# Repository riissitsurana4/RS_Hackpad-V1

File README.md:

# RS_Hackpad-V1

Hello everyone!
This is my first hardware project, built as part of **Blueprint (Hack Club)**.

It is a custom macropad made using switches, a rotatory encoder, oled display, etc.

---

## Case Design

The case consists of **two 3D-printed parts**

* **Top plate**
* **Base case**

---

## PCB Design

The PCB was designed in **KiCad** and includes the following features:

* **8 mechanical switches** arranged in a matrix (4 columns × 2 rows)
* **8 SK6812 RGB LEDs** for underglow
* **1 rotary encoder**
* **0.91 inch OLED display**
* **Seeed XIAO RP2040** as the MCU

The LEDs are placed near the edges of the PCB to create an underglow effect through the case.

---
## Final Design
Arranged 3D version of all the parts including the pcb.

---

## Firmware

I have made the firmware using **KMK**. 

I have only made basic firmware as it is very confusing and i do not have anything to test on.

---

## BOM

Seeed XIAO RP2040 

Through-hole 1N4148 Diodes (x9)

MX-Style switches (x8)

EC11 Rotary encoders (x1)

0.91 inch OLED displays

SK6812 MINI-E LEDs (x8)

M3x16mm screws & M3x5mx4mm heatset inserts

---

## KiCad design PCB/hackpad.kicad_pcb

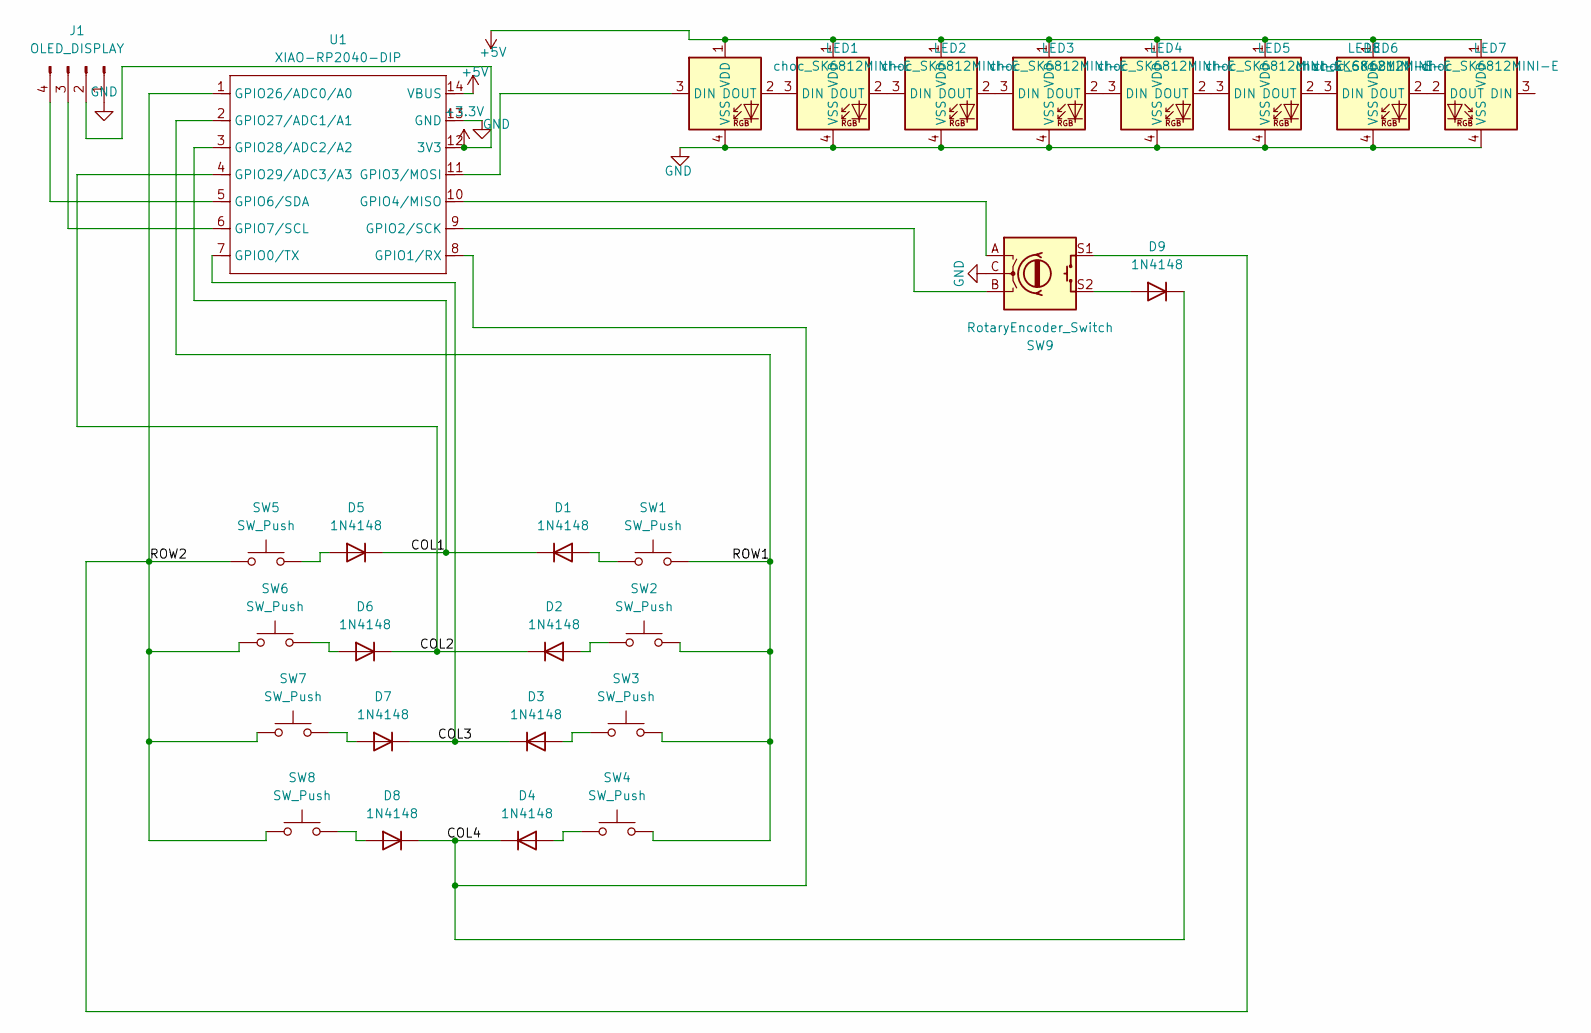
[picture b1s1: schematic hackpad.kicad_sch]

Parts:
D1, D2, D3, D4, D5, D6, D7, D8, D9: 1N4148; D_DO-35_SOD27_P7.62mm_Horizontal
J1: OLED_DISPLAY; PinHeader_1x04_P2.54mm_Vertical
LED1, LED2, LED3, LED4, LED5, LED6, LED7, LED8: choc_SK6812MINI-E; LED_SK6812MINI_PLCC4_3.5x3.5mm_P1.75mm
SW1, SW2, SW3, SW4, SW5, SW6, SW7, SW8: SW_Push; SW_Cherry_MX_1.00u_PCB
SW9: RotaryEncoder_Switch; RotaryEncoder_Alps_EC11E-Switch_Vertical_H20mm
U1: XIAO-RP2040-DIP

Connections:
+3.3V: J1.2, U1.12 (3V3)
+5V: LED1.1 (VDD), LED2.1 (VDD), LED3.1 (VDD), LED4.1 (VDD), LED5.1 (VDD), LED6.1 (VDD), LED7.1 (VDD), LED8.1 (VDD), U1.14 (VBUS)
/COL1: D1.1 (K), D5.1 (K), U1.3 (GPIO28/ADC2/A2)
/COL2: D2.1 (K), D6.1 (K), U1.4 (GPIO29/ADC3/A3)
/COL3: D3.1 (K), D7.1 (K), U1.7 (GPIO0/TX)
/COL4: D4.1 (K), D8.1 (K), D9.1 (K), U1.8 (GPIO1/RX)
/ROW1: SW1.1, SW2.1, SW3.1, SW4.1, U1.2 (GPIO27/ADC1/A1)
/ROW2: SW5.1, SW6.1, SW7.1, SW8.1, SW9.S1, U1.1 (GPIO26/ADC0/A0)
GND: J1.1, LED1.4 (VSS), LED2.4 (VSS), LED3.4 (VSS), LED4.4 (VSS), LED5.4 (VSS), LED6.4 (VSS), LED7.4 (VSS), LED8.4 (VSS), SW9.C, U1.13 (GND)
unnamed: D1.2 (A), SW1.2
unnamed: D2.2 (A), SW2.2
unnamed: D3.2 (A), SW3.2
unnamed: D4.2 (A), SW4.2
unnamed: D5.2 (A), SW5.2
unnamed: D6.2 (A), SW6.2
unnamed: D7.2 (A), SW7.2
unnamed: D8.2 (A), SW8.2
unnamed: D9.2 (A), SW9.S2
unnamed: J1.3, U1.6 (GPIO7/SCL)
unnamed: J1.4, U1.5 (GPIO6/SDA)
unnamed: LED1.3 (DIN), U1.11 (GPIO3/MOSI)
unnamed: LED1.2 (DOUT), LED2.3 (DIN)
unnamed: LED2.2 (DOUT), LED3.3 (DIN)
unnamed: LED3.2 (DOUT), LED4.3 (DIN)
unnamed: LED4.2 (DOUT), LED5.3 (DIN)
unnamed: LED5.2 (DOUT), LED6.3 (DIN)
unnamed: LED6.2 (DOUT), LED7.3 (DIN)
unnamed: LED7.2 (DOUT), LED8.2 (DOUT)
unnamed: SW9.B, U1.9 (GPIO2/SCK)
unnamed: SW9.A, U1.10 (GPIO4/MISO)

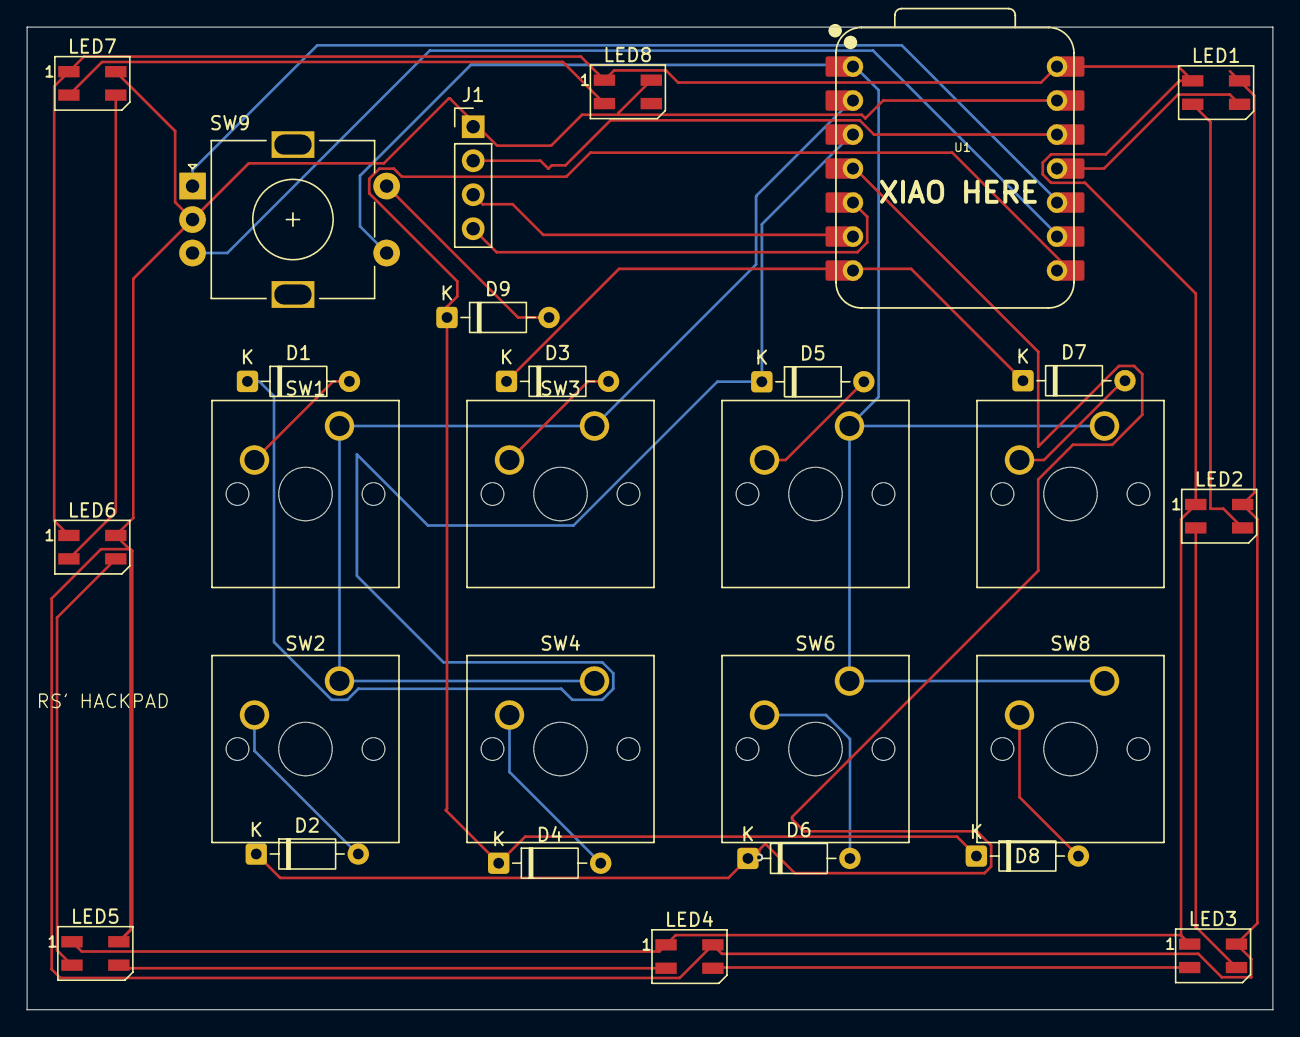
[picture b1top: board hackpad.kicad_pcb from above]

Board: 2 copper layers, 93.1 x 73.4 mm, 28 parts (0 on the bottom side), 30 nets.

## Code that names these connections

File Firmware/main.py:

import board
from kmk.kmk_keyboard import KMKKeyboard
from kmk.keys import KC
from kmk.scanners import DiodeOrientation

keyboard = KMKKeyboard()

keyboard.col_pins = (
    board.GPIO28,  # COL1
    board.GPIO29,  # COL2
    board.GPIO0,  # COL3
    board.GPIO1,  # COL4
)

keyboard.row_pins = (
    board.GPIO26,  # ROW1
    board.GPIO27,  # ROW2
)

keyboard.diode_orientation = DiodeOrientation.COL2ROW


keyboard.keymap = [
    [
        KC.Q, KC.W, KC.E, KC.R,
        KC.A, KC.S, KC.D, KC.F,
    ]
]


if __name__ == "__main__":
    keyboard.go()

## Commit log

2025-12-15 uploading necessary files
2025-12-16 uploading stuff
2025-12-16 Updated Readme
    Expanded the README to include detailed project information, including case design, PCB design, final design, and firmware details.
2025-12-17 adding BOM
2025-12-17 uploading files
    clearing drc
2026-03-23 adding blog.md
    Added a note about missing drill files for the PCB.
2026-03-26 update blog
